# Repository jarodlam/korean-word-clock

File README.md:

# Korean word clock
A wall-mounted clock that reads out the current time in Korean.

## Bill of materials
* Raspberry Pi Pico
    * [Core Electronics](https://core-electronics.com.au/raspberry-pi-pico.html)
* Pimoroni RV3028 Breakout
    * [Core Electronics](https://core-electronics.com.au/pimoroni-rv3028-real-time-clock-rtc-breakout.html)
* Adafruit USB-C Breakout
    * [Core Electronics](https://core-electronics.com.au/adafruit-usb-c-breakout-board-downstream-connection.html)
* 1000 uF electrolytic capacitor
    * [Core Electronics](https://core-electronics.com.au/electrolytic-decoupling-capacitors-1000uf-25v.html)
* 1N4733A 5.1 V Zener diode
    * [Core Electronics](https://core-electronics.com.au/zener-diode-5-1v-1w.html)
    * [Jaycar](https://www.jaycar.com.au/5-1v-1n4733-1-watt-zener-diode/p/ZR1403)
* LED 3-pin JST-SM pigtail connectors
    * [Core Electronics](https://core-electronics.com.au/led-strip-pigtail-connector-3-pin.html)
* 12mm momentary push button
    * [Core Electronics](https://core-electronics.com.au/momentary-push-button-switch-12mm-square.html)
    * [Jaycar](https://www.jaycar.com.au/spst-pcb-mount-tactile-switch-round/p/SP0609)

## Translations
Korean | English
------ | -------
한시 | one o'clock
두시 | two o'clock
세시 | three o'clock
네시 | four o'clock
다섯시 | five o'clock
여섯시 | six o'clock
일곱시 | seven o'clock
여덟시 | eight o'clock
아홉시 | nine o'clock
열시 | ten o'clock
열한시 | eleven o'clock
열두시 | twelve o'clock
자정 | midnight
정오 | noon
오분 | five minutes
십분 | ten minutes
이십분 | twenty minutes
삼십분 | thirty minutes
사십분 | forty minutes
오십분 | fifty minutes

## Acknowledgements
* [HangulClock](https://suapapa.github.io/site-hangulclocks/) by Homin Lee
* [Raspberry Pi Pico EAGLE library](https://github.com/Lobo-T/RPI-Pico-Eagle-lib) by Lobo-T
* [pi_pico_neopixel](https://github.com/blaz-r/pi_pico_neopixel) MicroPython library by Blaž Rolih
* [rv3028-python](https://github.com/pimoroni/rv3028-python) MicroPython library by Pimoroni

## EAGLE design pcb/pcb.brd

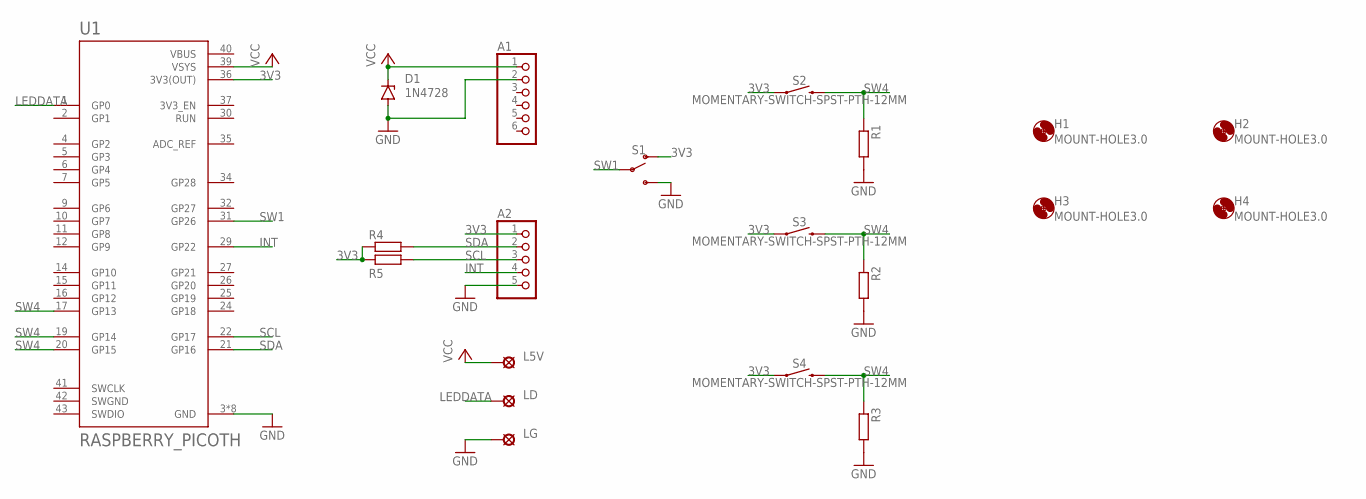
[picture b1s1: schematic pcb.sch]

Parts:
A1: PINHD-1X6; 1X06
A2: PINHD-1X5; 1X05
D1: 1N4728; DO41Z10
H1, H2, H3, H4: MOUNT-HOLE3.0; 3,0
L5V: LSP10
LD: LSP10
LG: LSP10
R1, R2, R3, R4, R5: R-EU_0207/7; 0207/7
S1: SWITCH-SPDT-PTH-11.6X4.0MM-LOCK; SWITCH_SPDT_PTH_11.6X4.0MM_LOCK
S2, S3, S4: MOMENTARY-SWITCH-SPST-PTH-12MM; TACTILE_SWITCH_PTH_12MM
U1: RASPBERRY_PICOTH; PICO-PKG-TH

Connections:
3V3: A2.1, R4.1, R5.1, S1.1 (O), S2.1, S3.1, S4.1, U1.36 (3V3(OUT))
GND: A1.2, A2.5, D1.A, LG.MP, R1.2, R2.2, R3.2, S1.3 (S), U1.3 (GND), U1.8 (GND), U1.13 (GND), U1.18 (GND), U1.23 (GND), U1.28 (GND), U1.33 (GND), U1.38 (GND)
INT: A2.4, U1.29 (GP22)
LEDDATA: LD.MP, U1.1 (GP0)
SCL: A2.3, R5.2, U1.22 (GP17)
SDA: A2.2, R4.2, U1.21 (GP16)
SW1: S1.2, U1.31 (GP26)
SW4: R1.1, R2.1, R3.1, S2.3 (2), S3.3 (2), S4.3 (2), U1.17 (GP13), U1.19 (GP14), U1.20 (GP15)
SWGND: U1.42 (SWGND)
VBUS: U1.40 (VBUS)
VCC: A1.1, D1.C, L5V.MP, U1.39 (VSYS)

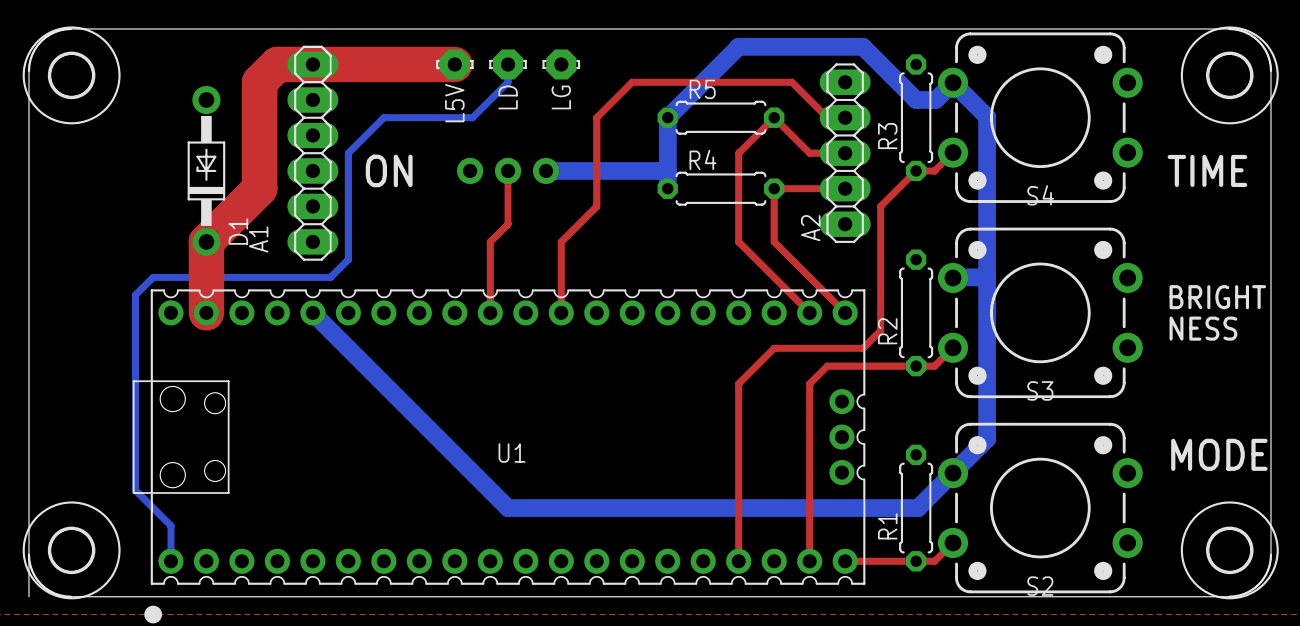
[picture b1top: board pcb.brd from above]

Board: 2 copper layers, 88.9 x 40.6 mm, 20 parts (1 on the bottom side), 9 nets.

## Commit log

2022-06-14 [CAD] CAD work in progress
2022-06-14 [CAD] Layer 2 and 3
2022-06-14 [CAD] Most layers done
2022-07-05 [PCB] Initial commit for PCB
2022-08-25 [CAD] Finish 3D design
2022-08-27 [DOC] Updated BOM
2022-08-29 [PCB] Finished design subject to testing
2022-08-29 [DOC] Translations and updated BOM
2022-08-30 [PCB] Sent off for manufacturing
2022-08-30 [CAD] Cutout size for PCB
2022-08-30 [SRC] Start on code
2022-08-30 [DOC] More translations
2022-09-14 [CAD] Mostly final design, need to fix front grid spacing
2022-09-14 [LASER] Start work on laser layout
2022-09-14 [CAD] Fix grid spacing
2022-09-14 [LASER] Final layout
2022-09-24 [SRC] RV2038 interface class
2022-09-24 [SRC] ClockFace class and effects
2022-09-25 [SRC] Button hook up and fast-forwarding
2022-09-25 [SRC] Move ButtonInput to a separate file
2022-09-25 [SRC] Scheduling system
2022-09-25 [SRC] Birthday effect and better rainbow effect
2022-09-30 [SRC] Set time script
2022-09-30 [SRC] Save settings to RTC EEPROM and more effects
2022-10-04 [SRC] Switch daylight savings on/off using switch
2023-06-25 [DOC] Change title
2024-11-22 [CHORE] Add v2
2024-11-22 [PCB] Start v2 PCB
2024-11-22 [DOC] Add additional BOM
2024-11-27 [PCB] New PCB mostly complete
2024-11-29 [DOC] Correct resistor
2024-11-29 [PCB] Final design and gerber
2025-01-11 [SRC] Button implementation
2025-01-12 [SRC] Port RV3028 library
2025-01-12 [SRC] RTC fully working
2025-03-29 [SRC] LED matrix code
2025-09-28 [SRC] Use PlatformIO
2025-09-28 [SRC] Run clang-format
2025-10-01 [SRC] Add Nix
2025-10-04 wip 2
2025-10-04 wip 3
2025-10-04 wip 4 (working)
2025-10-05 uploading!
2025-10-05 it works
2025-10-05 [SRC] KoreanClockFace implementation, refactor, tests
    wip 2
    wip 3
    wip 4 (working)
    uploading!
    it works
2025-10-05 [CHORE] Add Nix
2025-10-26 [SRC] clang-format
2025-10-27 [SRC] buttons wip
2025-10-27 [SRC] make buttons work
2025-12-17 [CAD] v2 mods
2025-12-17 [LASER] exports
2026-01-03 [LASER] layout

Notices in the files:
parts and their libraries:
SparkFun-Switches: Licensing: Creative Commons ShareAlike 4.0 International - https://creativecommons.org/licenses/by-sa/4.0
